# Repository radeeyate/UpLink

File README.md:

# UpLink

UpLink was a 491-gram high altitude balloon payload with a custom 3D printed
enclosure, a LoRa image downlink, and two independent trackers. It reached the
stratosphere, sent back hundreds of pictures, and we never recovered it.

You can read my full engineering writeup and see more details on [my website](https://radi8.dev/blog/uplink)

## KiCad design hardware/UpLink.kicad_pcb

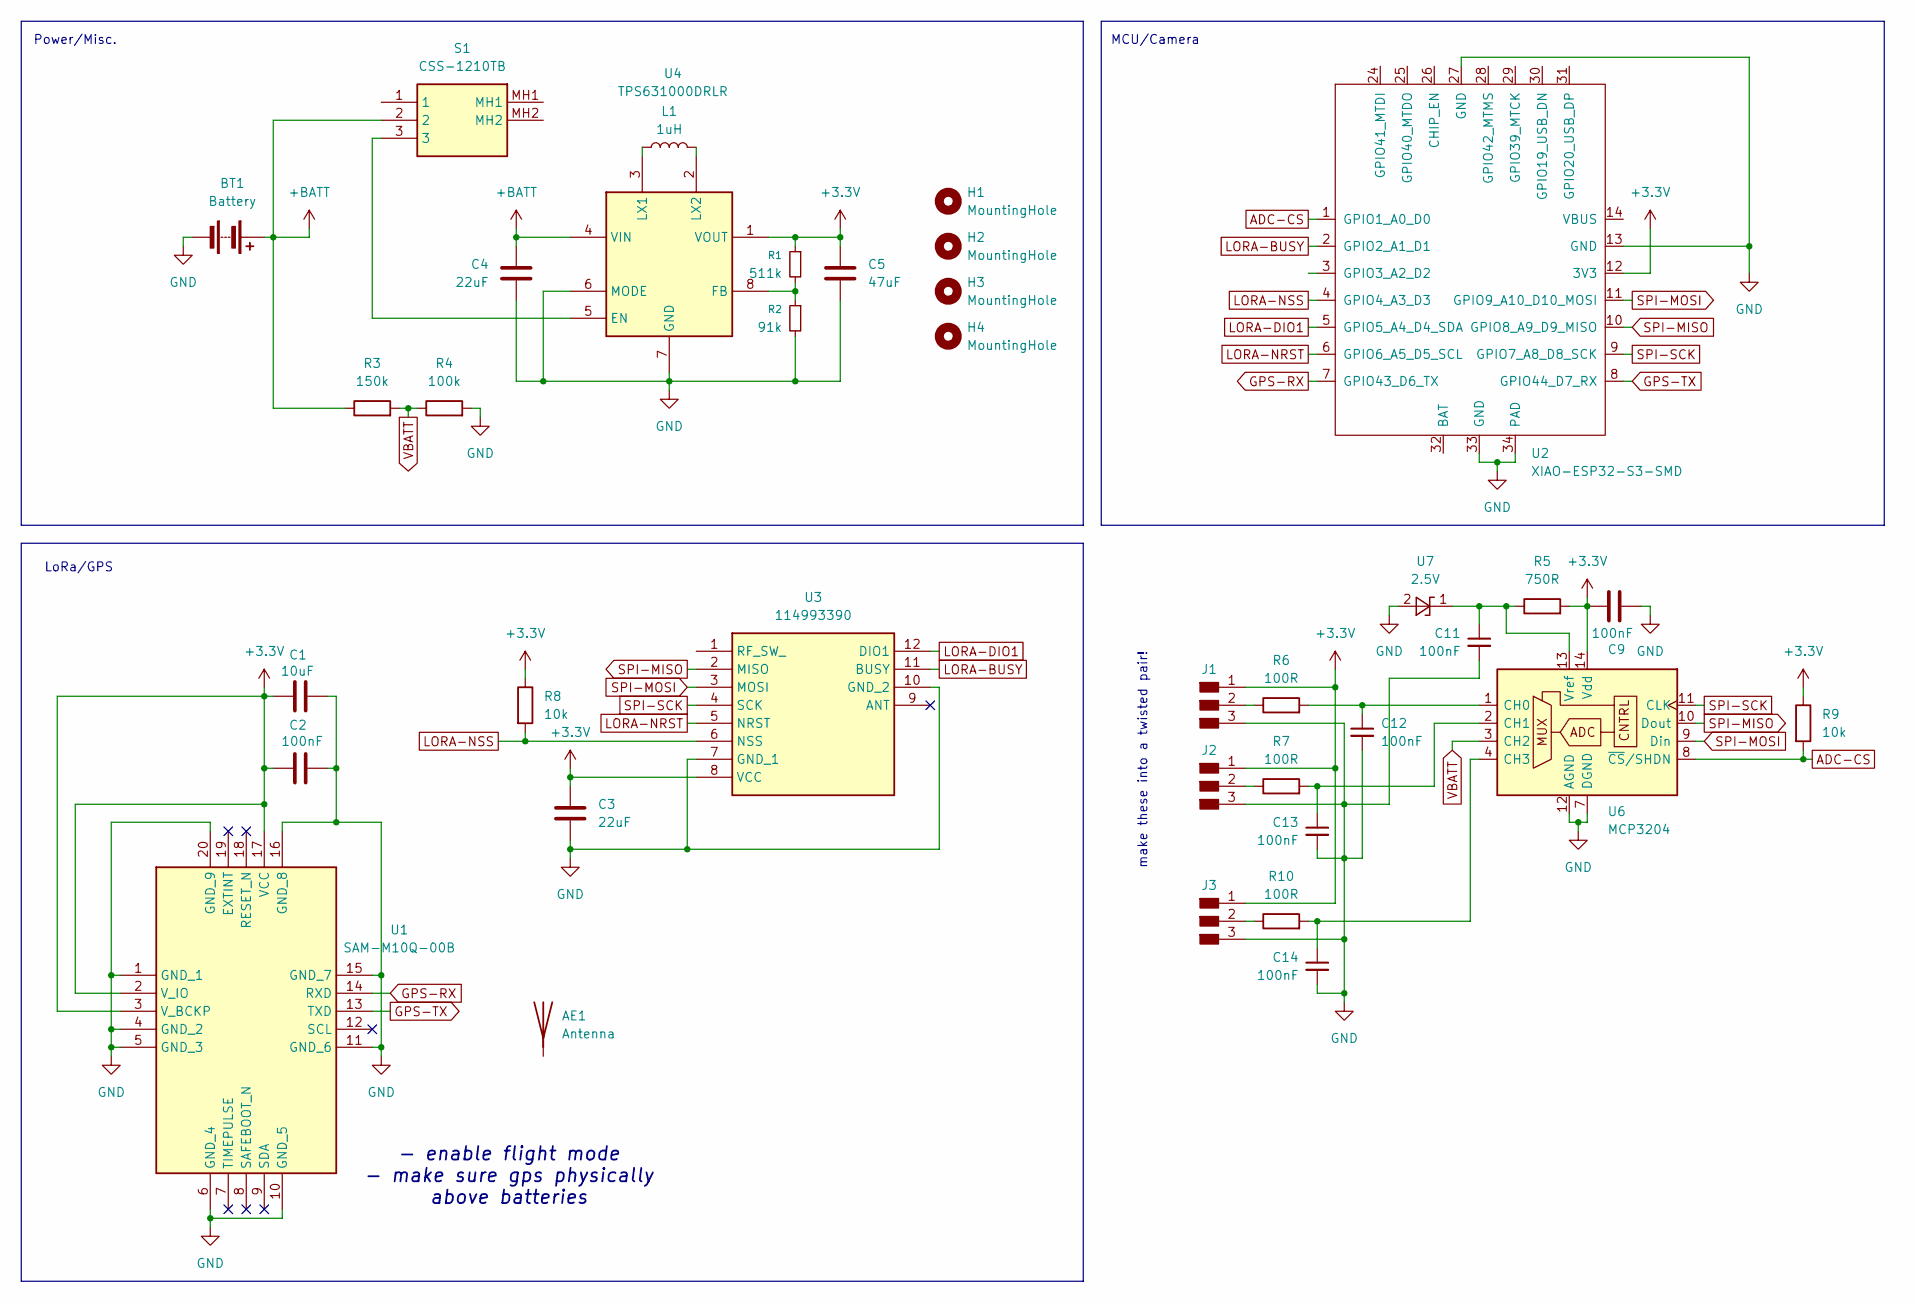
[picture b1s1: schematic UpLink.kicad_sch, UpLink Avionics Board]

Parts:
AE1: Antenna; Mouser Part 713-110061501
BT1: Battery; PinHeader_1x02_P2.54mm_Vertical; Mouser Part 12BHC431A-GR
C1: 10uF; C_0805_2012Metric; Mouser Part 81-GRM21BR71A106KA3L
C2, C9, C11, C12, C13, C14: 100nF; C_0603_1608Metric; Mouser Part 603-CC603KRX7R7BB104
C3, C4: 22uF; C_0805_2012Metric; Mouser Part 81-GRM21BZ71A226ME5L
C5: 47uF; C_0805_2012Metric; Mouser Part 81-GRM21BZ71A226ME5L
H1, H2, H3, H4: MountingHole; MountingHole_2.2mm_M2_Pad
J1, J2, J3: PinHeader_01x03_P2.54mm_Vertical_THT_D1mm; PinHeader_1x03_P1.27mm_Vertical; Mouser Part 595-LMT87LPGM
L1: 1uH; L_1008_2520Metric; Mouser Part 81-DFE252012F-1R0MP2
R1: 511k; R_0603_1608Metric; Mouser Part 603-RT0603FRE07511KL
R2: 91k; R_0603_1608Metric; Mouser Part 603-AC0603JR-0791KL
R3: 150k; R_0603_1608Metric; Mouser Part 603-RC0603JR-07150KL
R4: 100k; R_0603_1608Metric; Mouser Part 603-AC0603FR-07100KL
R5: 750R; R_0603_1608Metric; Mouser Part 603-RC0603FR-13750RL
R6, R7, R10: 100R; R_0603_1608Metric; Mouser Part 603-AC0603FR-13100RL
R8, R9: 10k; R_0603_1608Metric; Mouser Part 603-RC0603FR-0710KL
S1: CSS-1210TB; CSS1210TB; Mouser Part Number 229-CSS-1210TB
U1: SAM-M10Q-00B; SAMM10Q00B; Mouser Part Number 377-SAM-M10Q-00B
U2: XIAO-ESP32-S3-SMD; Mouser Part 713-113991115
U3: 114993390; Mouser Part 713-114993390
U4: TPS631000DRLR; SOTFL50P160X60-8N; Mouser Part Number 595-TPS631000DRLR
U6: MCP3204; TSSOP-14_4.4x5mm_P0.65mm; Mouser Part MCP3204-CI/ST
U7: 2.5V; SOT-23-3; Mouser Part 998-LM4040CYM3-2.5TR

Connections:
+3.3V: C1.1, C2.1, C3.1, C5.1, C9.2, J1.1, J2.1, J3.1, R1.1, R5.2, R8.1, R9.1, U1.2 (V_IO), U1.3 (V_BCKP), U1.17 (VCC), U2.12 (3V3), U3.8 (VCC), U4.1 (VOUT), U6.14 (Vdd)
+BATT: BT1.1 (+), C4.1, R3.1, S1.2, U4.4 (VIN)
ADC-CS: R9.2, U2.1 (GPIO1_A0_D0), U6.8 (~CS/SHDN)
GND: BT1.2 (-), C1.2, C2.2, C3.2, C4.2, C5.2, C9.1, C11.2, C12.2, C13.2, C14.2, J1.3, J2.3, J3.3, R2.2, R4.2, U1.1 (GND_1), U1.4 (GND_2), U1.5 (GND_3), U1.6 (GND_4), U1.10 (GND_5), U1.11 (GND_6), U1.15 (GND_7), U1.16 (GND_8), U1.20 (GND_9), U2.13 (GND), U2.27 (GND), U2.33 (GND), U2.34 (PAD), U3.7 (GND_1), U3.10 (GND_2), U4.6 (MODE), U4.7 (GND), U6.7 (DGND), U6.12 (AGND), U7.2 (A)
GPS-RX: U1.14 (RXD), U2.7 (GPIO43_D6_TX)
GPS-TX: U1.13 (TXD), U2.8 (GPIO44_D7_RX)
LORA-BUSY: U2.2 (GPIO2_A1_D1), U3.11 (BUSY)
LORA-DIO1: U2.5 (GPIO5_A4_D4_SDA), U3.12 (DIO1)
LORA-NRST: U2.6 (GPIO6_A5_D5_SCL), U3.5 (NRST)
LORA-NSS: R8.2, U2.4 (GPIO4_A3_D3), U3.6 (NSS)
unnamed: J1.2, R6.1
unnamed: J2.2, R7.1
unnamed: J3.2, R10.1
unnamed: S1.3, U4.5 (EN)
unnamed: R1.2, R2.1, U4.8 (FB)
unnamed: L1.1, U4.3 (LX1)
unnamed: L1.2, U4.2 (LX2)
unnamed: C12.1, R6.2, U6.1 (CH0)
unnamed: C13.1, R7.2, U6.2 (CH1)
unnamed: C14.1, R10.2, U6.4 (CH3)
unnamed: C11.1, R5.1, U6.13 (Vref), U7.1 (K)
SPI-MISO: U2.10 (GPIO8_A9_D9_MISO), U3.2 (MISO), U6.10 (Dout)
SPI-MOSI: U2.11 (GPIO9_A10_D10_MOSI), U3.3 (MOSI), U6.9 (Din)
SPI-SCK: U2.9 (GPIO7_A8_D8_SCK), U3.4 (SCK), U6.11 (CLK)
VBATT: R3.2, R4.1, U6.3 (CH2)

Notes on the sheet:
LoRa/GPS
MCU/Camera
- enable flight mode - make sure gps physically above batteries
Power/Misc.
make these into a twisted pair!

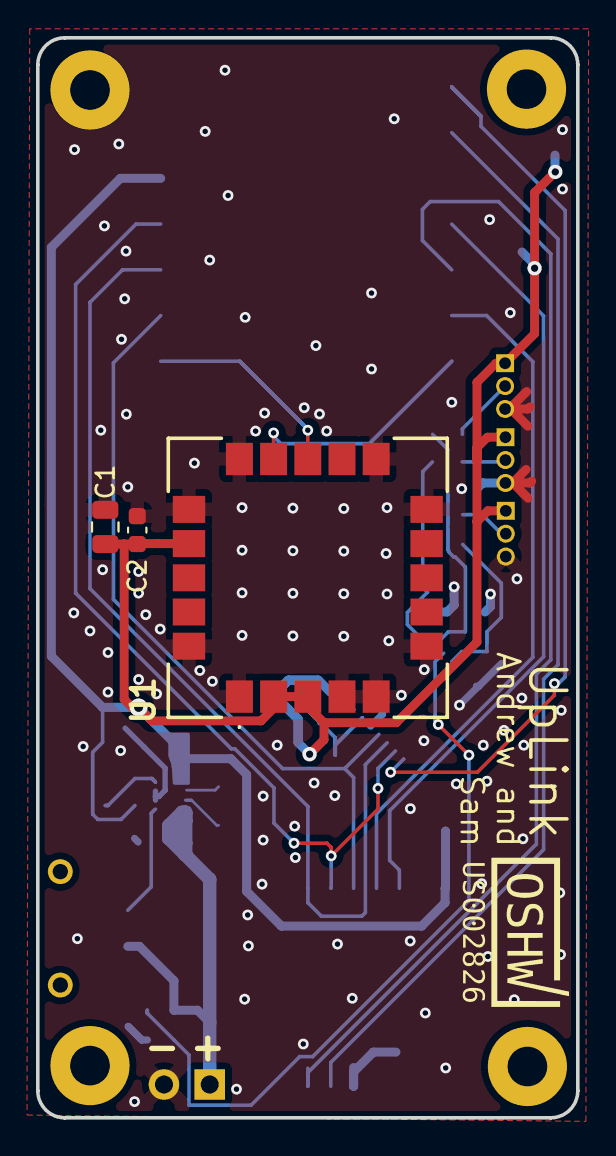
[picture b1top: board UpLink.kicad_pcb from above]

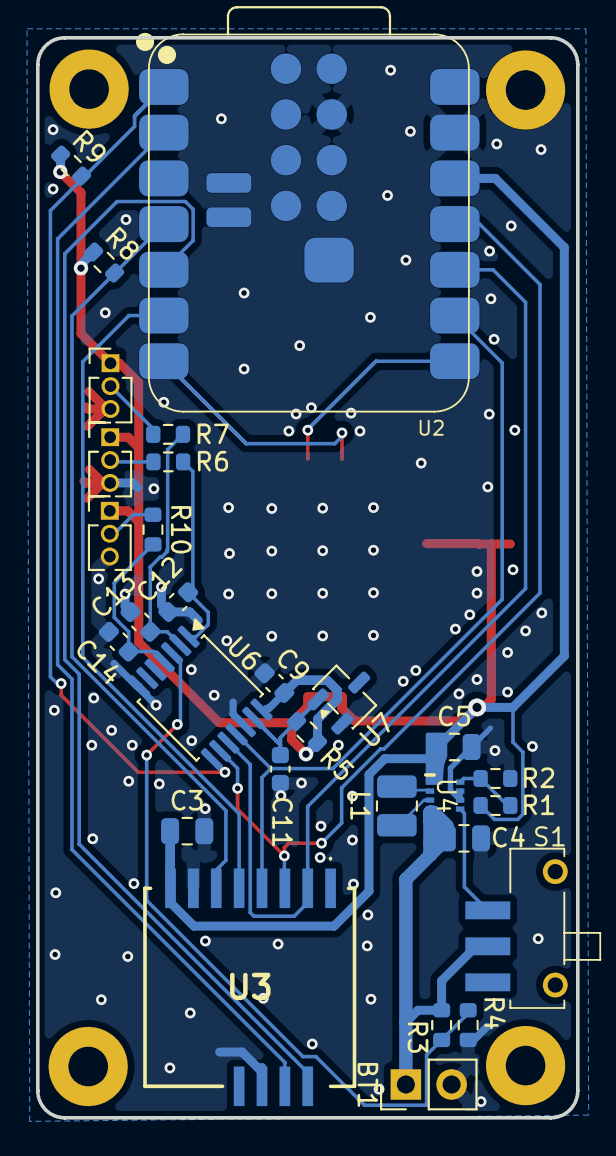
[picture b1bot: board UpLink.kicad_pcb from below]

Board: 2 copper layers, 30.0 x 60.0 mm, 36 parts (29 on the bottom side), 25 nets.

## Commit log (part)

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2026-04-23 Clean up schematic
2026-04-24 Add TPS22917DBV for high side switching of payload, redesign layout for thinner board at cost of slight GPS performance hits
2026-04-24 Add notes to schematic
2026-04-25 Redo layout and routing, space traces apart
2026-04-27 not sure what I did here but
2026-04-27 delete
2026-04-27 Add ADC for temp sensors and battery voltage
2026-04-27 Save project
2026-04-27 Update to KiCad 10
2026-04-27 add license
2026-04-27 Add MIT license
2026-04-27 remove vbatt label floating
2026-04-28 Assign some unassigned parts for Mouser
2026-04-29 Remove ferrite beads from power, add LM4040 for 2.5V ref for MCP3204
2026-04-30 kinda forgot what I did here
2026-05-01 add oshwa logo, uplink text
2026-05-02 Untested listener code for reciving datapackets
2026-05-02 Working dashboard tied to csv inputs
2026-05-02 Offline Map functionality
2026-05-02 Add initial SSDV testing code, have it write to SD card
2026-05-02 Altitude and time based graphing
2026-05-02 Refactored date convertion to /utils/dateUtils.ts. Added time tooltip to GPS
2026-05-02 Stats bar and design changes
2026-05-02 add telem sending in packets
2026-05-02 PCB changes
2026-05-03 Get SSDV working over RTL-SDR
2026-05-03 Pushing Dateutils
2026-05-23 Added scrub bar, plotly temperature graph, and go to home button for GPS
2026-05-24 update hardware
2026-05-24 Update RTL-SDR listener script
2026-05-24 Use 16 bit int for SSDV image ID
2026-05-24 listener
2026-05-24 remove files
2026-05-25 dashboard telem stuff
2026-05-25 no cache images
2026-05-25 optimize the dashboard
2026-06-02 pcb fixed in case I remake these in the future
2026-06-04 rtlsdr listener updates
2026-06-04 Add rfm95 listener script
2026-06-13 Update firmware/listener
2026-06-13 Lower serial wait to 5000ms, increase GNSS nav rate, only send telem every 3rd packet
2026-06-13 Fix RTL-SDR listener, update dashboard
2026-06-13 Lower SSDV packet size to 128 bytes
2026-06-14 Make telem be sent all the time rather than every few SSDV packets
2026-06-14 dashboard
2026-06-15 "will it work?"
2026-06-15 update decoder
2026-06-15 Disable bluetooth/wifi, switch to CR5 for better reception, sleep radio in between packets to save some power
2026-06-17 Use 2 points of precision for GPS, lower SSDV frame quality, send timestamp if no GPS fix, load AGPS data from SD card, increase WDT timeout, and save SSDV state to avoid overwriting images
2026-06-17 batt voltage
2026-06-19 - use absolute path for .ssdv_state - write \n for SSDV state - isolate telemetry transmission into sendTelemetry() - still send gps coordinates if no fix is reported - continue into loop() if camera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
2026-06-19 add missing semicolon
